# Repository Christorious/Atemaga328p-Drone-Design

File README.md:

# Atemaga328p-Drone-Design
PCB design of MicroDrone. It was design in Kicad 6 but it is done but for just a few design rules errors still to be done .

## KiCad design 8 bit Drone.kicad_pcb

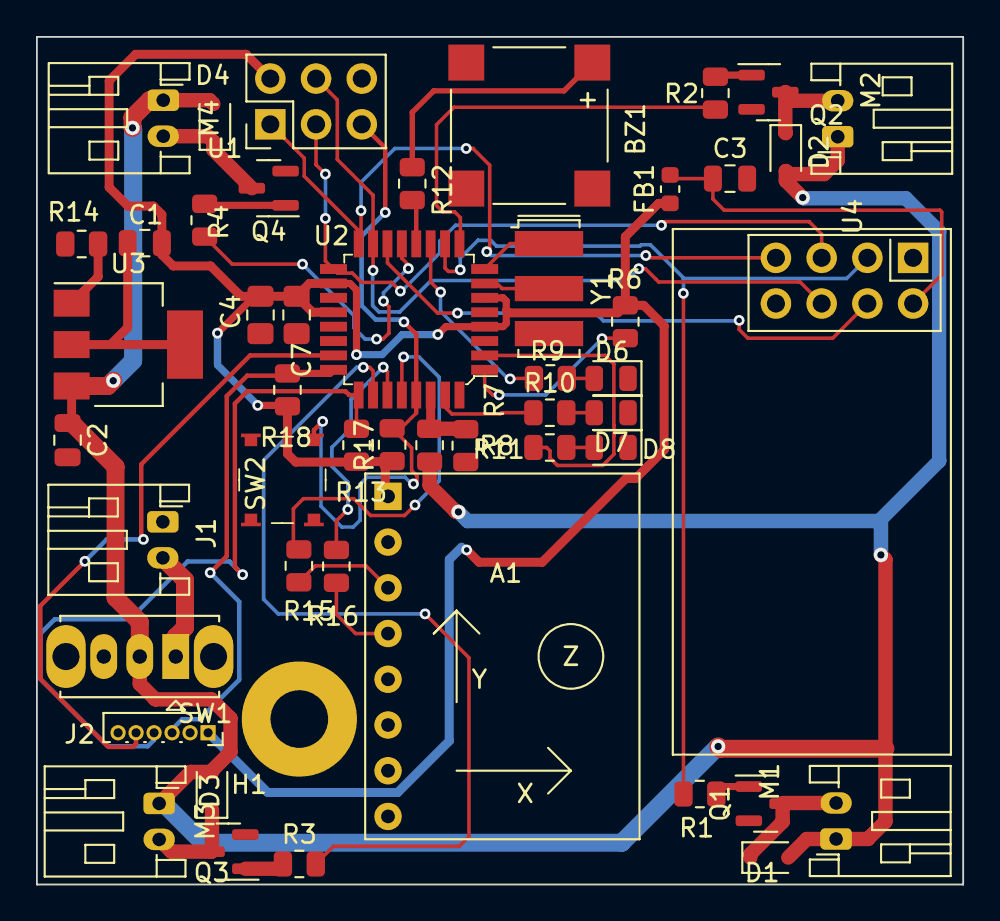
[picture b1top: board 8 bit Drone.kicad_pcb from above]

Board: 2 copper layers, 51.5 x 47.1 mm, 50 parts (0 on the bottom side), 43 nets.

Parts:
A1: MPU6050_Module
BZ1: Buzzer; PUIAudio_SMT_0825_S_4_R
C1, C3: 10µF; C_0805_2012Metric
C2: 100µF; C_0805_2012Metric
C4, C7: 0.1µF; C_0805_2012Metric_Pad1.18x1.45mm_HandSolder
D1, D2, D3, D4: DIODE; D_SOD-323
D6, D7, D8: LED; LED_0805_2012Metric
FB1: FerriteBead_Small; L_0603_1608Metric
H1: MountingHole; MountingHole_3.2mm_M3_Pad
J1: BAT1; JST_PH_S2B-PH-K_1x02_P2.00mm_Horizontal
J2: Conn_01x06_MountingPin; PinSocket_1x06_P1.00mm_Vertical
M1, M2, M3, M4: Motor_DC_ALT; JST_PH_S2B-PH-K_1x02_P2.00mm_Horizontal
Q1, Q2, Q3, Q4: 2N7002E; SOT-23
R1, R2, R3, R4: R100Ω_US; R_0805_2012Metric
R6, R7: 100R; R_0805_2012Metric
R8: 470R; R_0805_2012Metric
R9: R330_US; R_0805_2012Metric
R10, R11: R1k_US; R_0805_2012Metric
R12: 330R; R_0805_2012Metric
R13, R18: 10k; R_0805_2012Metric
R14: R470Ω; R_0805_2012Metric
R15, R16: 4.7kR; R_0805_2012Metric
R17: 10kΩ; R_0805_2012Metric
SW1: SW_SPST; SW_Slide_1P2T_CK_OS102011MS2Q
SW2: RST_SW; Switch_Tactile_SMD_4.5x4.5mm_TL3315NF160Q
U1: AVR-ISP-6; PinHeader_2x03_P2.54mm_Vertical
U2: ATMEGA328P-AU-ND; TQFP-32_7x7mm
U3: AMS1117-3.3; SOT-223-3_TabPin2
U4: NRF24L01_Breakout; nRF24L01_Breakout
Y1: Crystal_GND3_Small; Resonator_SMD-3Pin_7.2x3.0mm

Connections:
+3.3V: A1.1 (VCC), C1.1, C4.1, C7.1, FB1.1, J2.1, R6.2, R13.2, R17.1, R18.2, U1.2 (VCC), U2.4 (VCC), U2.6 (VCC), U2.18 (AVCC), U2.20 (AREF)
BLUE: R11.1, U2.2 (PD4)
CSN: U2.14 (PB2), U4.4 (~CSN)
GND: A1.2 (GND), A1.7 (AD0), BZ1.2 (+), C2.2, C3.2, C4.2, C7.2, D6.1 (K), D7.1 (K), D8.1 (K), J1.1, J2.2, Q1.2 (S), Q2.2 (S), Q3.2 (S), Q4.2 (S), R8.2, R14.1, SW2.2 (B), U1.6 (GND), U2.3 (GND), U2.5 (GND), U2.21 (GND), U4.1 (GND), Y1.3
GREEN: R10.1, U2.31 (PD1)
MISO: U1.1 (MISO), U2.16 (PB4), U4.7 (MISO)
MOSI: U1.4 (MOSI), U2.15 (PB3), U4.6 (MOSI)
NSS: R6.1, U2.1 (PD3)
unnamed: A1.3 (SCL), R15.2
unnamed: A1.4 (SDA), R16.1
unnamed: BZ1.1 (-), R12.2
unnamed: C1.2, U3.2 (VO)
unnamed: C3.1, FB1.2, U4.2 (VCC)
unnamed: D1.1 (A), M1.2 (-), Q1.3 (D)
unnamed: D2.1 (A), M2.2 (-), Q2.3 (D)
unnamed: D3.1 (A), M3.2 (-), Q3.3 (D)
unnamed: D4.1 (A), M4.2 (-), Q4.3 (D)
unnamed: D6.2 (A), R9.2
unnamed: D7.2 (A), R10.2
unnamed: D8.2 (A), R11.2
unnamed: J1.2, SW1.1 (A)
unnamed: Q1.1 (G), R1.1
unnamed: Q2.1 (G), R2.1
unnamed: Q3.1 (G), R3.1
unnamed: Q4.1 (G), R4.1
unnamed: R12.1, U2.12 (PB0)
unnamed: R14.2, U3.1 (GND)
unnamed: U2.7 (PB6), Y1.2
unnamed: U2.8 (PB7), Y1.1
PB1: R4.2, U2.13 (PB1)
PC0: J2.5, U2.23 (PC0)
PC3: R3.2, U2.26 (PC3)
PD5: R2.2, U2.9 (PD5)
PD6: R1.2, U2.10 (PD6), U4.3 (CE)
RED: R9.1, U2.11 (PD7)
RST: R17.2, SW2.1 (A), U1.5 (~RST), U2.29 (PC6)
SCK: U1.3 (SCK), U2.17 (PB5), U4.5 (SCK)
SCL: R15.1, U2.28 (PC5)
SCL1: J2.3, R18.1, U2.24 (PC1)
SDA: R16.2, U2.27 (PC4)
SDA1: J2.4, R13.1, U2.25 (PC2)
VCC: C2.1, D1.2 (K), D2.2 (K), D3.2 (K), D4.2 (K), M1.1 (+), M2.1 (+), M3.1 (+), M4.1 (+), R7.1, SW1.2 (B), U3.3 (VI)
VDD: R7.2, R8.1, U2.30 (PD0)
